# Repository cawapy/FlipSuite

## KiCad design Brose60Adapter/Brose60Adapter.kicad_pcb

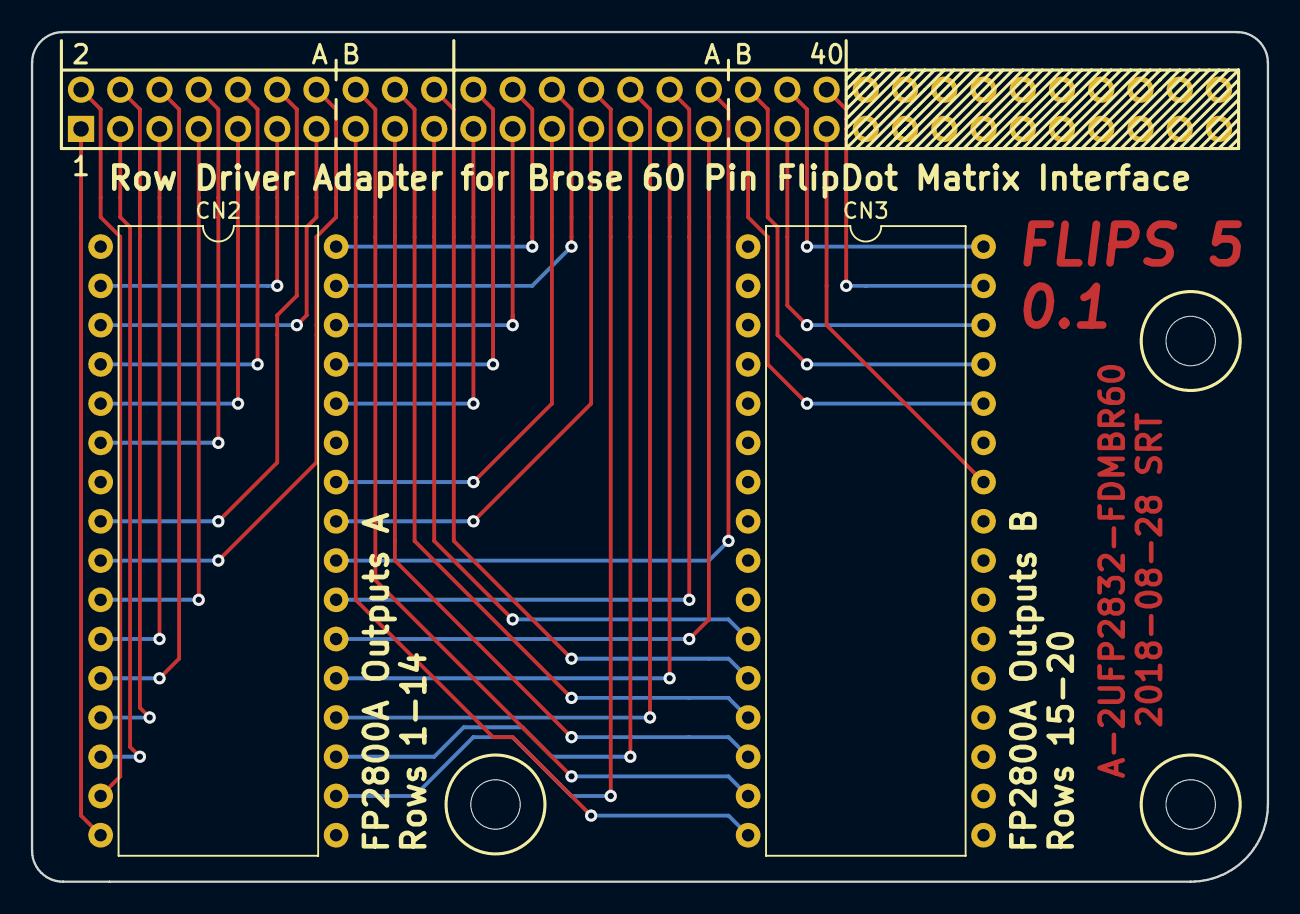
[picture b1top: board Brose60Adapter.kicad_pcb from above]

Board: 2 copper layers, 80.0 x 55.0 mm, 3 parts (1 on the bottom side), 40 nets.

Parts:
CN1: Conn_02x30_Odd_Even; Socket_Strip_Straight_2x30_Pitch2.54mm
CN2, CN3: FP2800A; DIP-32-from-40_W15.24mm

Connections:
unnamed: CN1.1, CN2.16
unnamed: CN1.2, CN2.15
unnamed: CN1.3, CN2.14
unnamed: CN1.4, CN2.13
unnamed: CN1.5, CN2.11
unnamed: CN1.6, CN2.12
unnamed: CN1.7, CN2.10
unnamed: CN1.8, CN2.6
unnamed: CN1.9, CN2.5
unnamed: CN1.10, CN2.4
unnamed: CN1.11, CN2.2
unnamed: CN1.12, CN2.8
unnamed: CN1.13, CN2.3
unnamed: CN1.14, CN2.9
unnamed: CN1.15, CN3.16
unnamed: CN1.16, CN3.15
unnamed: CN1.17, CN3.14
unnamed: CN1.18, CN3.13
unnamed: CN1.19, CN3.11
unnamed: CN1.20, CN3.12
unnamed: CN1.21, CN2.36
unnamed: CN1.22, CN2.37
unnamed: CN1.23, CN2.38
unnamed: CN1.24, CN2.40
unnamed: CN1.25, CN2.34
unnamed: CN1.26, CN2.39
unnamed: CN1.27, CN2.33
unnamed: CN1.28, CN2.26
unnamed: CN1.29, CN2.27
unnamed: CN1.30, CN2.28
unnamed: CN1.31, CN2.29
unnamed: CN1.32, CN2.31
unnamed: CN1.33, CN2.30
unnamed: CN1.34, CN2.32
unnamed: CN1.35, CN3.36
unnamed: CN1.36, CN3.37
unnamed: CN1.37, CN3.38
unnamed: CN1.38, CN3.40
unnamed: CN1.39, CN3.34
unnamed: CN1.40, CN3.39

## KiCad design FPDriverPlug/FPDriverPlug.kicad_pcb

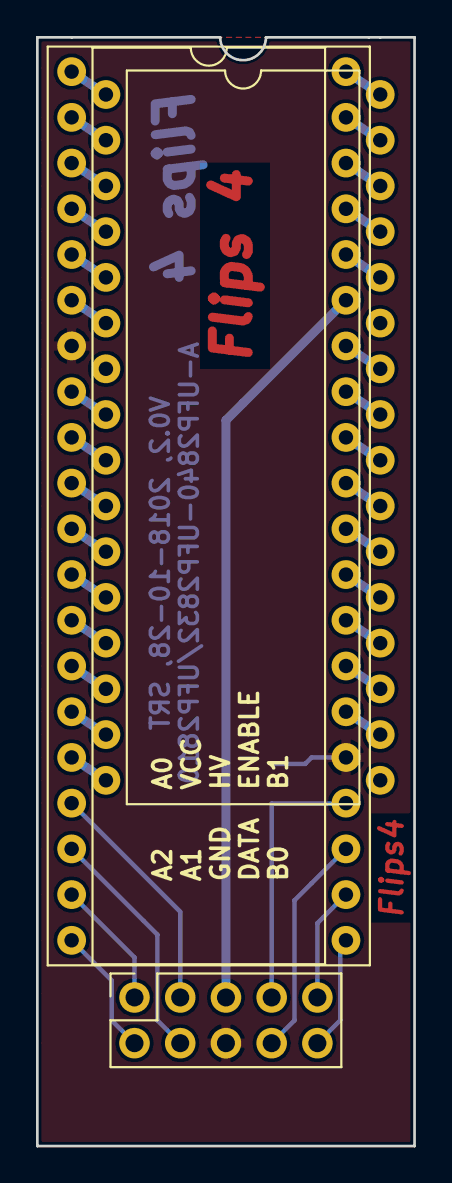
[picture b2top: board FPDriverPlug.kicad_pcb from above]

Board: 2 copper layers, 21.0 x 61.6 mm, 4 parts (1 on the bottom side), 39 nets.

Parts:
CN1: Conn_02x05_Odd_Even; Socket_Strip_Straight_2x05_Pitch2.54mm
CN2: Conn_02x16_Counter_Clockwise; DIP-32_W15.24mm
R1: 10K/OPT; R_0603_HandSoldering
U1: FP2800A; DIP-40_W15.24mm_Socket

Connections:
+12V: CN1.5, U1.35
/A0: CN1.1, U1.19
/A1: CN1.4, U1.18
/A2: CN1.2, U1.20
/B0: CN1.10, U1.21
/B1: CN1.9, U1.22
/Data: CN1.8, U1.23
/Enable: CN1.7, R1.1, U1.24
GND: CN1.6, R1.2, U1.7, U1.25
unnamed: CN2.1, U1.1
unnamed: CN2.2, U1.2
unnamed: CN2.3, U1.3
unnamed: CN2.4, U1.4
unnamed: CN2.5, U1.5
unnamed: CN2.6, U1.6
unnamed: CN2.8, U1.8
unnamed: CN2.9, U1.9
unnamed: CN2.10, U1.10
unnamed: CN2.11, U1.11
unnamed: CN2.12, U1.12
unnamed: CN2.13, U1.13
unnamed: CN2.14, U1.14
unnamed: CN2.15, U1.15
unnamed: CN2.16, U1.16
unnamed: CN2.18, U1.26
unnamed: CN2.19, U1.27
unnamed: CN2.20, U1.28
unnamed: CN2.21, U1.29
unnamed: CN2.22, U1.30
unnamed: CN2.23, U1.31
unnamed: CN2.24, U1.32
unnamed: CN2.25, U1.33
unnamed: CN2.26, U1.34
unnamed: CN2.28, U1.36
unnamed: CN2.29, U1.37
unnamed: CN2.30, U1.38
unnamed: CN2.31, U1.39
unnamed: CN2.32, U1.40
VCC: CN1.3, U1.17

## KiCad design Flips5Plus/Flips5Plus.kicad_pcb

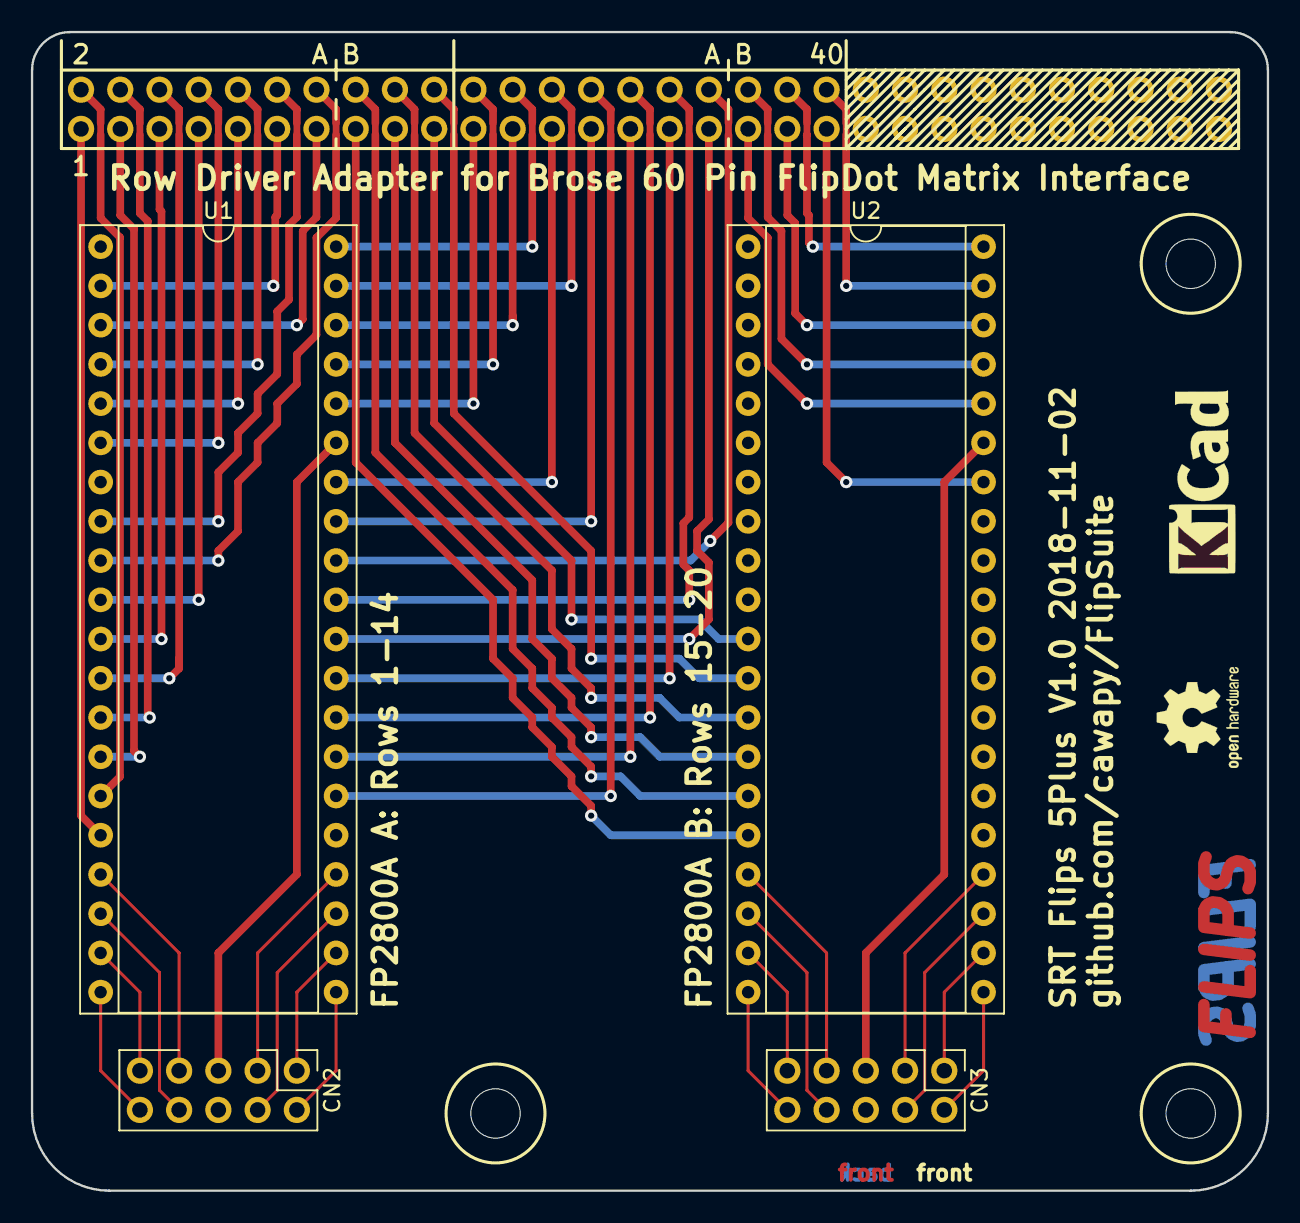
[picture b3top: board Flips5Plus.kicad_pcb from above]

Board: 2 copper layers, 80.0 x 75.0 mm, 5 parts (1 on the bottom side), 60 nets.

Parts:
CN1: Conn_02x30_Odd_Even; Socket_Strip_Straight_2x30_Pitch2.54mm
CN2, CN3: UFP2810; Pin_Header_Angle_Shrouded_2x05_Pitch2.54mm
U1, U2: FP2800A; DIP-40_W15.24mm_Socket

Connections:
/L.A0: CN2.9, U1.19
/L.A1: CN2.8, U1.18
/L.A2: CN2.10, U1.20
/L.B0: CN2.2, U1.21
/L.B1: CN2.1, U1.22
/L.EN: CN2.3, U1.24
/L.GND: CN2.6, U1.7, U1.25
/L.HV: CN2.5, U1.35
/L.POL: CN2.4, U1.23
/L.VCC: CN2.7, U1.17
/R.A0: CN3.9, U2.19
/R.A1: CN3.8, U2.18
/R.A2: CN3.10, U2.20
/R.B0: CN3.2, U2.21
/R.B1: CN3.1, U2.22
/R.EN: CN3.3, U2.24
/R.GND: CN3.6, U2.7, U2.25
/R.HV: CN3.5, U2.35
/R.POL: CN3.4, U2.23
/R.VCC: CN3.7, U2.17
unnamed: CN1.1, U1.16
unnamed: CN1.2, U1.15
unnamed: CN1.3, U1.14
unnamed: CN1.4, U1.13
unnamed: CN1.5, U1.11
unnamed: CN1.6, U1.12
unnamed: CN1.7, U1.10
unnamed: CN1.8, U1.6
unnamed: CN1.9, U1.5
unnamed: CN1.10, U1.4
unnamed: CN1.11, U1.2
unnamed: CN1.12, U1.8
unnamed: CN1.13, U1.3
unnamed: CN1.14, U1.9
unnamed: CN1.15, U2.16
unnamed: CN1.16, U2.15
unnamed: CN1.17, U2.14
unnamed: CN1.18, U2.13
unnamed: CN1.19, U2.11
unnamed: CN1.20, U2.12
unnamed: CN1.21, U1.36
unnamed: CN1.22, U1.37
unnamed: CN1.23, U1.38
unnamed: CN1.24, U1.40
unnamed: CN1.25, U1.34
unnamed: CN1.26, U1.39
unnamed: CN1.27, U1.33
unnamed: CN1.28, U1.26
unnamed: CN1.29, U1.27
unnamed: CN1.30, U1.28
unnamed: CN1.31, U1.29
unnamed: CN1.32, U1.31
unnamed: CN1.33, U1.30
unnamed: CN1.34, U1.32
unnamed: CN1.35, U2.36
unnamed: CN1.36, U2.37
unnamed: CN1.37, U2.38
unnamed: CN1.38, U2.40
unnamed: CN1.39, U2.34
unnamed: CN1.40, U2.39

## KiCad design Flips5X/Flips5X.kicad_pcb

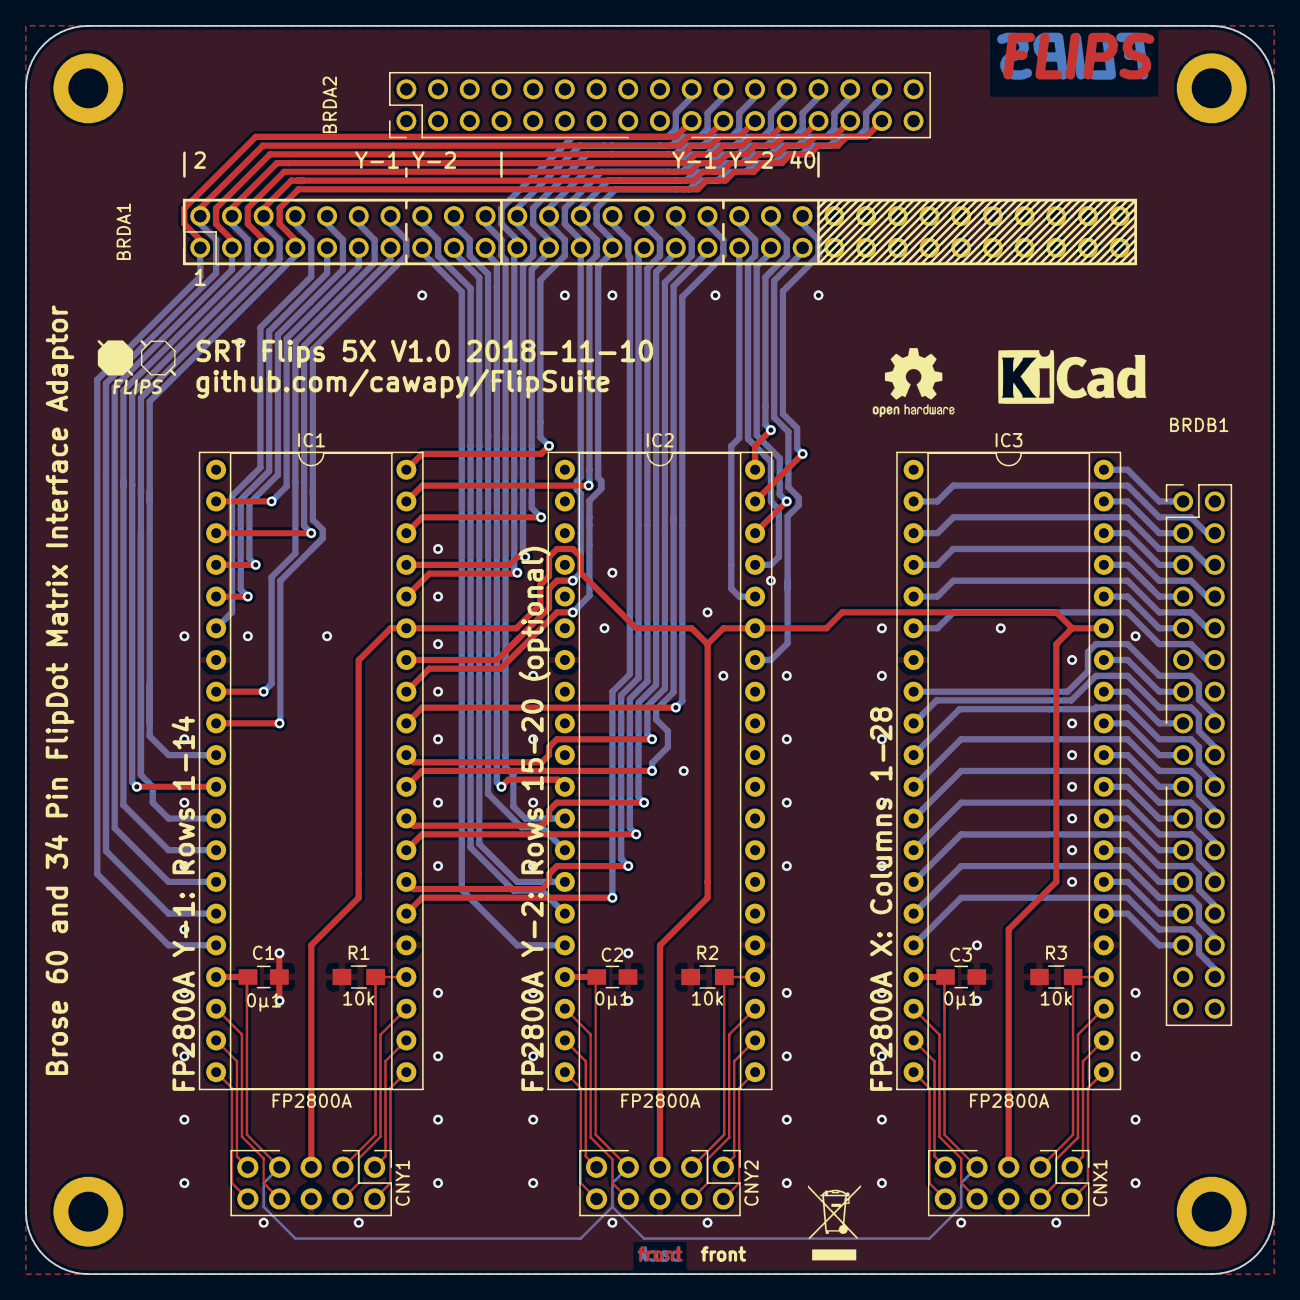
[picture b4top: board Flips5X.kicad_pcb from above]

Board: 2 copper layers, 100.0 x 100.0 mm, 15 parts (0 on the bottom side), 92 nets.

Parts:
BRDA1: Conn_02x30_Odd_Even; Pin_Header_Straight_Shrouded_2x30_Pitch2.54mm_ConvNumbering
BRDA2: Conn_02x17_Odd_Even; Pin_Header_Angle_Shrouded_2x17_Pitch2.54mm_ConvNumbering
BRDB1: Conn_02x17_Odd_Even; Pin_Header_Angle_Shrouded_2x17_Pitch2.54mm_ConvNumbering
C1, C2, C3: 0μ1; C_0805_HandSoldering
CNX1: UFP2810; Pin_Header_Angle_Shrouded_2x05_Pitch2.54mm
CNY1, CNY2: UFP2810; Pin_Header_Angle_Shrouded_2x05_Pitch2.54mm
IC1, IC2, IC3: FP2800A; DIP-40_W15.24mm_Socket
R1, R2, R3: 10k; R_0805_HandSoldering

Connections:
/GND: C1.1, C2.2, C3.2, CNX1.6, CNY1.6, CNY2.6, IC1.7, IC1.25, IC2.7, IC2.25, IC3.7, IC3.25, R1.1, R2.1, R3.1
/HV: CNX1.5, CNY1.5, CNY2.5, IC1.35, IC2.35, IC3.35
/SY1: BRDA1.1, BRDA2.19, IC1.16
/SY2: BRDA1.2, BRDA2.21, IC1.15
/SY3: BRDA1.3, BRDA2.23, IC1.14
/SY4: BRDA1.4, BRDA2.25, IC1.13
/SY5: BRDA1.5, BRDA2.27, IC1.11
/SY6: BRDA1.6, BRDA2.29, IC1.12
/SY7: BRDA1.7, BRDA2.31, IC1.10
/SY8: BRDA1.8, IC1.6
/SY9: BRDA1.9, IC1.5
/SY10: BRDA1.10, IC1.4
/SY11: BRDA1.11, IC1.2
/SY12: BRDA1.12, IC1.8
/SY13: BRDA1.13, IC1.3
/SY14: BRDA1.14, IC1.9
/SY15: BRDA1.15, IC2.16
/SY16: BRDA1.16, IC2.15
/SY17: BRDA1.17, IC2.14
/SY18: BRDA1.18, IC2.13
/SY19: BRDA1.19, IC2.11
/SY20: BRDA1.20, IC2.12
/VCC: C1.2, C2.1, C3.1, CNX1.7, CNY1.7, CNY2.7, IC1.17, IC2.17, IC3.17
/X1: BRDB1.32, IC3.16
/X2: BRDB1.30, IC3.15
/X3: BRDB1.28, IC3.14
/X4: BRDB1.26, IC3.13
/X5: BRDB1.22, IC3.11
/X6: BRDB1.24, IC3.12
/X7: BRDB1.20, IC3.10
/X8: BRDB1.12, IC3.6
/X9: BRDB1.10, IC3.5
/X10: BRDB1.8, IC3.4
/X11: BRDB1.4, IC3.2
/X12: BRDB1.16, IC3.8
/X13: BRDB1.6, IC3.3
/X14: BRDB1.18, IC3.9
/X15: BRDB1.9, IC3.36
/X16: BRDB1.7, IC3.37
/X17: BRDB1.5, IC3.38
/X18: BRDB1.1, IC3.40
/X19: BRDB1.13, IC3.34
/X20: BRDB1.3, IC3.39
/X21: BRDB1.15, IC3.33
/X22: BRDB1.29, IC3.26
/X23: BRDB1.27, IC3.27
/X24: BRDB1.25, IC3.28
/X25: BRDB1.23, IC3.29
/X26: BRDB1.19, IC3.31
/X27: BRDB1.21, IC3.30
/X28: BRDB1.17, IC3.32
/X.A0: CNX1.9, IC3.19
/X.A1: CNX1.8, IC3.18
/X.A2: CNX1.10, IC3.20
/X.B0: CNX1.2, IC3.21
/X.B1: CNX1.1, IC3.22
/X.EN: CNX1.3, IC3.24, R3.2
/X.POL: CNX1.4, IC3.23
/Y1.A0: CNY1.9, IC1.19
/Y1.A1: CNY1.8, IC1.18
/Y1.A2: CNY1.10, IC1.20
/Y1.B0: CNY1.2, IC1.21
/Y1.B1: CNY1.1, IC1.22
/Y1.EN: CNY1.3, IC1.24, R1.2
/Y1.POL: CNY1.4, IC1.23
/Y2.A0: CNY2.9, IC2.19
/Y2.A1: CNY2.8, IC2.18
/Y2.A2: CNY2.10, IC2.20
/Y2.B0: CNY2.2, IC2.21
/Y2.B1: CNY2.1, IC2.22
/Y2.EN: CNY2.3, IC2.24, R2.2
/Y2.POL: CNY2.4, IC2.23
/~RY1: BRDA1.21, BRDA2.20, IC1.36
/~RY2: BRDA1.22, BRDA2.22, IC1.37
/~RY3: BRDA1.23, BRDA2.24, IC1.38
/~RY4: BRDA1.24, BRDA2.26, IC1.40
/~RY5: BRDA1.25, BRDA2.28, IC1.34
/~RY6: BRDA1.26, BRDA2.30, IC1.39
/~RY7: BRDA1.27, BRDA2.32, IC1.33
/~RY8: BRDA1.28, IC1.26
/~RY9: BRDA1.29, IC1.27
/~RY10: BRDA1.30, IC1.28
/~RY11: BRDA1.31, IC1.29
/~RY12: BRDA1.32, IC1.31
/~RY13: BRDA1.33, IC1.30
/~RY14: BRDA1.34, IC1.32
/~RY15: BRDA1.35, IC2.36
/~RY16: BRDA1.36, IC2.37
/~RY17: BRDA1.37, IC2.38
/~RY18: BRDA1.38, IC2.40
/~RY19: BRDA1.39, IC2.34
/~RY20: BRDA1.40, IC2.39

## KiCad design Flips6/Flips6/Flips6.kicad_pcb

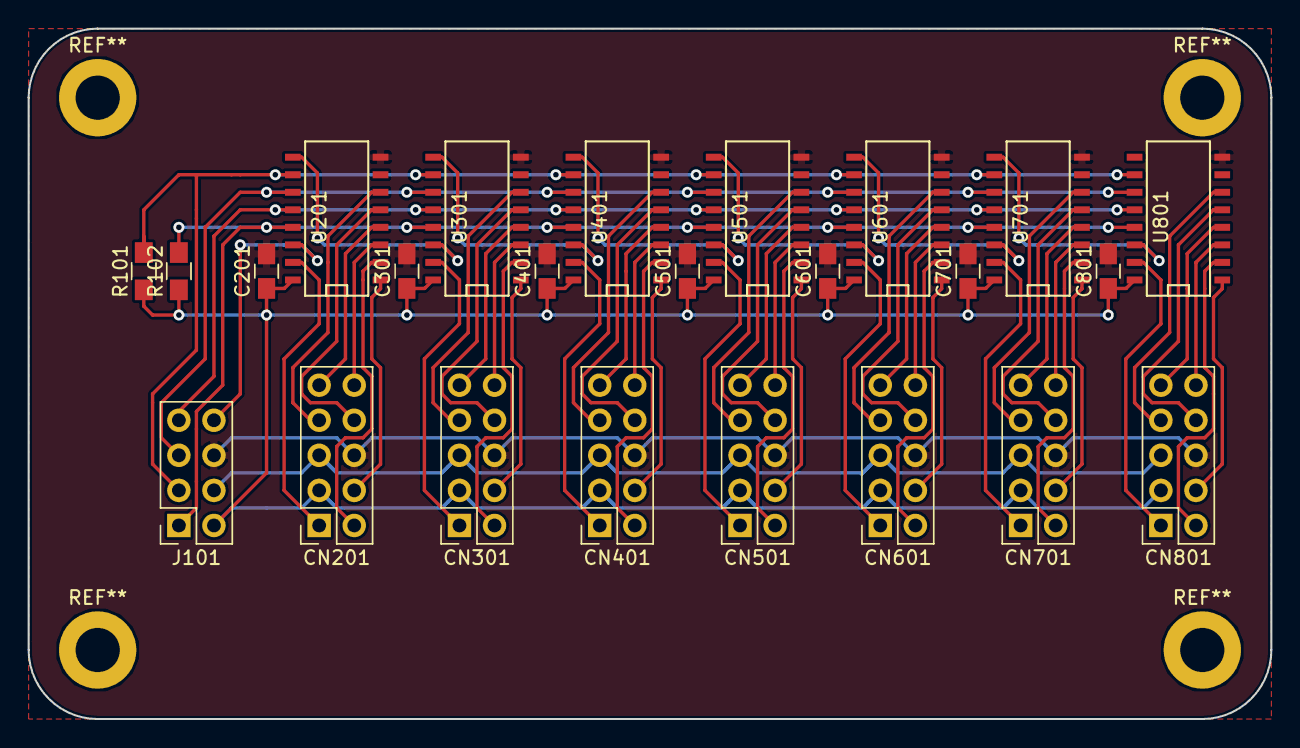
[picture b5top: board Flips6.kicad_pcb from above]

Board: 2 copper layers, 90.0 x 50.0 mm, 24 parts (0 on the bottom side), 63 nets.

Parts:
C201, C301, C401, C501, C601, C701, C801: 0u1; C_0805_HandSoldering
CN201, CN301, CN401, CN501, CN601, CN701, CN801: Conn_02x05_Odd_Even; Socket_Strip_Straight_2x05_Pitch2.54mm
J101: Conn_02x04_Odd_Even; Socket_Strip_Straight_2x04_Pitch2.54mm
R101, R102: 10K; R_0805_HandSoldering
U201, U301, U401, U501, U601, U701, U801: 74HCT595; SO-16-N

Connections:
+5V: C201.1, C301.1, C401.1, C501.1, C601.1, C701.1, C801.1, CN201.3, CN301.3, CN401.3, CN501.3, CN601.3, CN701.3, CN801.3, J101.2, R101.1, R102.1, U201.16, U301.16, U401.16, U501.16, U601.16, U701.16, U801.16
+12V: CN201.5, CN301.5, CN401.5, CN501.5, CN601.5, CN701.5, CN801.5, J101.4
/ShiftRegister2/A0: CN201.1, U201.15
/ShiftRegister2/A1: CN201.4, U201.1
/ShiftRegister2/A2: CN201.2, U201.2
/ShiftRegister2/B0: CN201.10, U201.3
/ShiftRegister2/B1: CN201.9, U201.4
/ShiftRegister2/DATA: CN201.8, U201.5
/ShiftRegister2/DIN: J101.8, U201.14
/ShiftRegister2/EN: CN201.7, U201.6
/ShiftRegister3/A0: CN301.1, U301.15
/ShiftRegister3/A1: CN301.4, U301.1
/ShiftRegister3/A2: CN301.2, U301.2
/ShiftRegister3/B0: CN301.10, U301.3
/ShiftRegister3/B1: CN301.9, U301.4
/ShiftRegister3/DATA: CN301.8, U301.5
/ShiftRegister3/DIN: U201.9, U301.14
/ShiftRegister3/EN: CN301.7, U301.6
/ShiftRegister4/A0: CN401.1, U401.15
/ShiftRegister4/A1: CN401.4, U401.1
/ShiftRegister4/A2: CN401.2, U401.2
/ShiftRegister4/B0: CN401.10, U401.3
/ShiftRegister4/B1: CN401.9, U401.4
/ShiftRegister4/DATA: CN401.8, U401.5
/ShiftRegister4/DIN: U301.9, U401.14
/ShiftRegister4/EN: CN401.7, U401.6
/ShiftRegister5/A0: CN501.1, U501.15
/ShiftRegister5/A1: CN501.4, U501.1
/ShiftRegister5/A2: CN501.2, U501.2
/ShiftRegister5/B0: CN501.10, U501.3
/ShiftRegister5/B1: CN501.9, U501.4
/ShiftRegister5/DATA: CN501.8, U501.5
/ShiftRegister5/DIN: U401.9, U501.14
/ShiftRegister5/EN: CN501.7, U501.6
/ShiftRegister6/A0: CN601.1, U601.15
/ShiftRegister6/A1: CN601.4, U601.1
/ShiftRegister6/A2: CN601.2, U601.2
/ShiftRegister6/B0: CN601.10, U601.3
/ShiftRegister6/B1: CN601.9, U601.4
/ShiftRegister6/DATA: CN601.8, U601.5
/ShiftRegister6/DIN: U501.9, U601.14
/ShiftRegister6/EN: CN601.7, U601.6
/ShiftRegister7/A0: CN701.1, U701.15
/ShiftRegister7/A1: CN701.4, U701.1
/ShiftRegister7/A2: CN701.2, U701.2
/ShiftRegister7/B0: CN701.10, U701.3
/ShiftRegister7/B1: CN701.9, U701.4
/ShiftRegister7/DATA: CN701.8, U701.5
/ShiftRegister7/DIN: U601.9, U701.14
/ShiftRegister7/EN: CN701.7, U701.6
/ShiftRegister8/A0: CN801.1, U801.15
/ShiftRegister8/A1: CN801.4, U801.1
/ShiftRegister8/A2: CN801.2, U801.2
/ShiftRegister8/B0: CN801.10, U801.3
/ShiftRegister8/B1: CN801.9, U801.4
/ShiftRegister8/DATA: CN801.8, U801.5
/ShiftRegister8/DIN: U701.9, U801.14
/ShiftRegister8/EN: CN801.7, U801.6
GND: C201.2, C301.2, C401.2, C501.2, C601.2, C701.2, C801.2, CN201.6, CN301.6, CN401.6, CN501.6, CN601.6, CN701.6, CN801.6, J101.6, U201.8, U301.8, U401.8, U501.8, U601.8, U701.8, U801.8
RCLK: J101.7, U201.12, U301.12, U401.12, U501.12, U601.12, U701.12, U801.12
SRCLK: J101.5, U201.11, U301.11, U401.11, U501.11, U601.11, U701.11, U801.11
~OE: J101.1, R102.2, U201.13, U301.13, U401.13, U501.13, U601.13, U701.13, U801.13
~SRCLR: J101.3, R101.2, U201.10, U301.10, U401.10, U501.10, U601.10, U701.10, U801.10

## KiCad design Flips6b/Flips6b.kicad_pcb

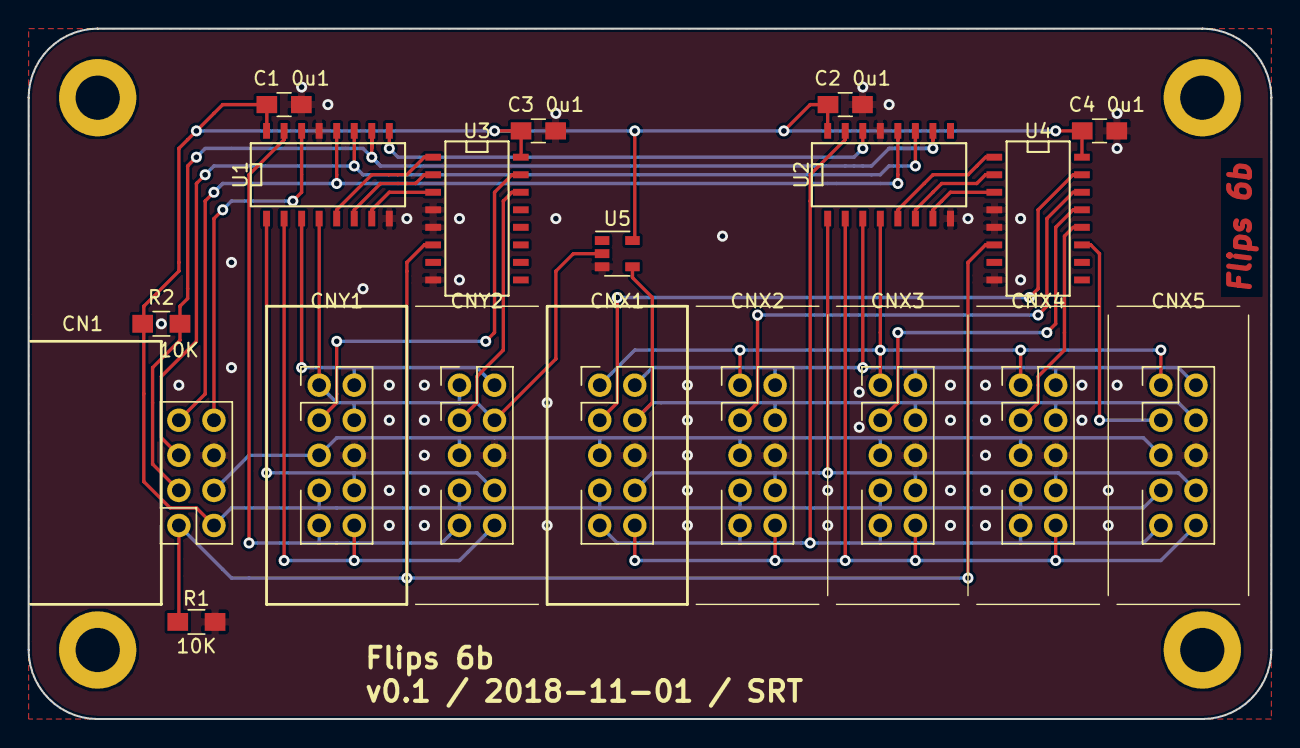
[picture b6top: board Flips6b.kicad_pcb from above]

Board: 2 copper layers, 90.0 x 50.0 mm, 19 parts (0 on the bottom side), 33 nets.

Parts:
C1, C2, C3, C4: 0u1; C_0805_HandSoldering
CN1: Conn_02x04_Odd_Even; Socket_Strip_Straight_2x04_Pitch2.54mm
CNX1, CNX2, CNX3, CNX4, CNX5: UFP2810; Pin_Header_Straight_Shrouded_2x05_Pitch2.54mm
CNY1, CNY2: UFP2810; Pin_Header_Straight_Shrouded_2x05_Pitch2.54mm
R1, R2: 10K; R_0805_HandSoldering
U1, U2: 74HCT595; SO-16-N
U3, U4: 74HC238; SO-16-N
U5: 74LVC1G04; SOT-23-5

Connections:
+5V: C1.1, C2.1, C3.1, C4.1, CN1.2, CNX1.7, CNX2.7, CNX3.7, CNX4.7, CNX5.7, CNY1.7, CNY2.7, R2.2, U1.16, U2.16, U3.16, U4.16, U5.5
+12V: CN1.4, CNX1.5, CNX2.5, CNX3.5, CNX4.5, CNX5.5, CNY1.5, CNY2.5
/DIN: CN1.8, U1.14
/ENABLE: CN1.1, R1.1, U3.6, U4.6
/POL: CNY1.1, CNY1.4, CNY2.1, CNY2.4, U1.4, U5.2
/RCLK: CN1.7, U1.12, U2.12
/SRCLK: CN1.5, U1.11, U2.11
/XA0: CNX1.9, CNX2.9, CNX3.9, CNX4.9, CNX5.9, U2.15
/XA1: CNX1.8, CNX2.8, CNX3.8, CNX4.8, CNX5.8, U2.1
/XA2: CNX1.10, CNX2.10, CNX3.10, CNX4.10, CNX5.10, U2.2
/XB0: CNX1.2, CNX2.2, CNX3.2, CNX4.2, CNX5.2, U2.3
/XB1: CNX1.1, CNX2.1, CNX3.1, CNX4.1, CNX5.1, U2.4
/XC0: U2.5, U4.1
/XC1: U2.6, U4.2
/XC2: U2.7, U4.3
/XD: CNX1.4, CNX2.4, CNX3.4, CNX4.4, CNX5.4, U5.4
/XE.0: CNX1.3, U4.15
/XE.1: CNX2.3, U4.14
/XE.2: CNX3.3, U4.13
/XE.3: CNX4.3, U4.12
/XE.4: CNX5.3, U4.11
/YA0: CNY1.9, CNY2.9, U1.15
/YA1: CNY1.8, CNY2.8, U1.1
/YA2: CNY1.10, CNY2.10, U1.2
/YB0: CNY1.2, CNY2.2, U1.3
/YC0: U1.5, U3.1
/YC1: U1.6, U3.2
/YC2: U1.7, U3.3
/YE.0: CNY1.3, U3.15
/YE.1: CNY2.3, U3.14
/~SRCLR: CN1.3, R2.1, U1.10, U2.10
GND: C1.2, C2.2, C3.2, C4.2, CN1.6, CNX1.6, CNX2.6, CNX3.6, CNX4.6, CNX5.6, CNY1.6, CNY2.6, R1.2, U1.8, U1.13, U2.8, U2.13, U3.4, U3.5, U3.8, U4.4, U4.5, U4.8, U5.3
unnamed: U1.9, U2.14
